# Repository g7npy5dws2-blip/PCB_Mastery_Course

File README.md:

# PCB_Mastery_Course
Here will be all the documents assosiated with the PCB_Mastery_Course

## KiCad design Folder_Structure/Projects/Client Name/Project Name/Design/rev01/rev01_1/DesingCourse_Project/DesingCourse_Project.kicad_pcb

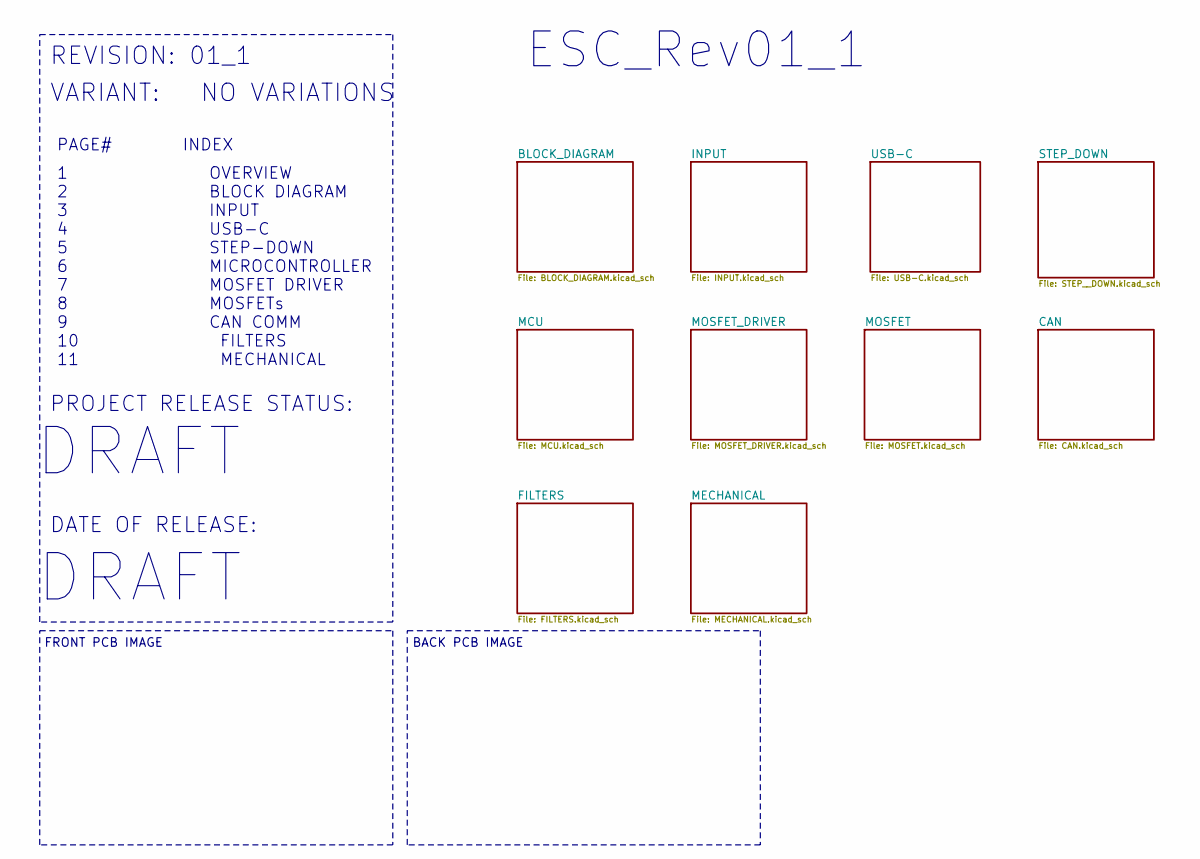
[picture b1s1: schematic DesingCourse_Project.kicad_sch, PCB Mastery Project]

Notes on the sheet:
VARIANT:
NO VARIATIONS
1 OVERVIEW 2 BLOCK DIAGRAM 3 INPUT 4 USB-C 5 STEP-DOWN 6 MICROCONTROLLER 7 MOSFET DRIVER 8 MOSFETs 9 CAN COMM 10 FILTERS 11 MECHANICAL
PAGE# INDEX
DRAFT
PROJECT RELEASE STATUS: DATE OF RELEASE:
ESC_Rev01_1
FRONT PCB IMAGE
REVISION: ${REVISION}
BACK PCB IMAGE

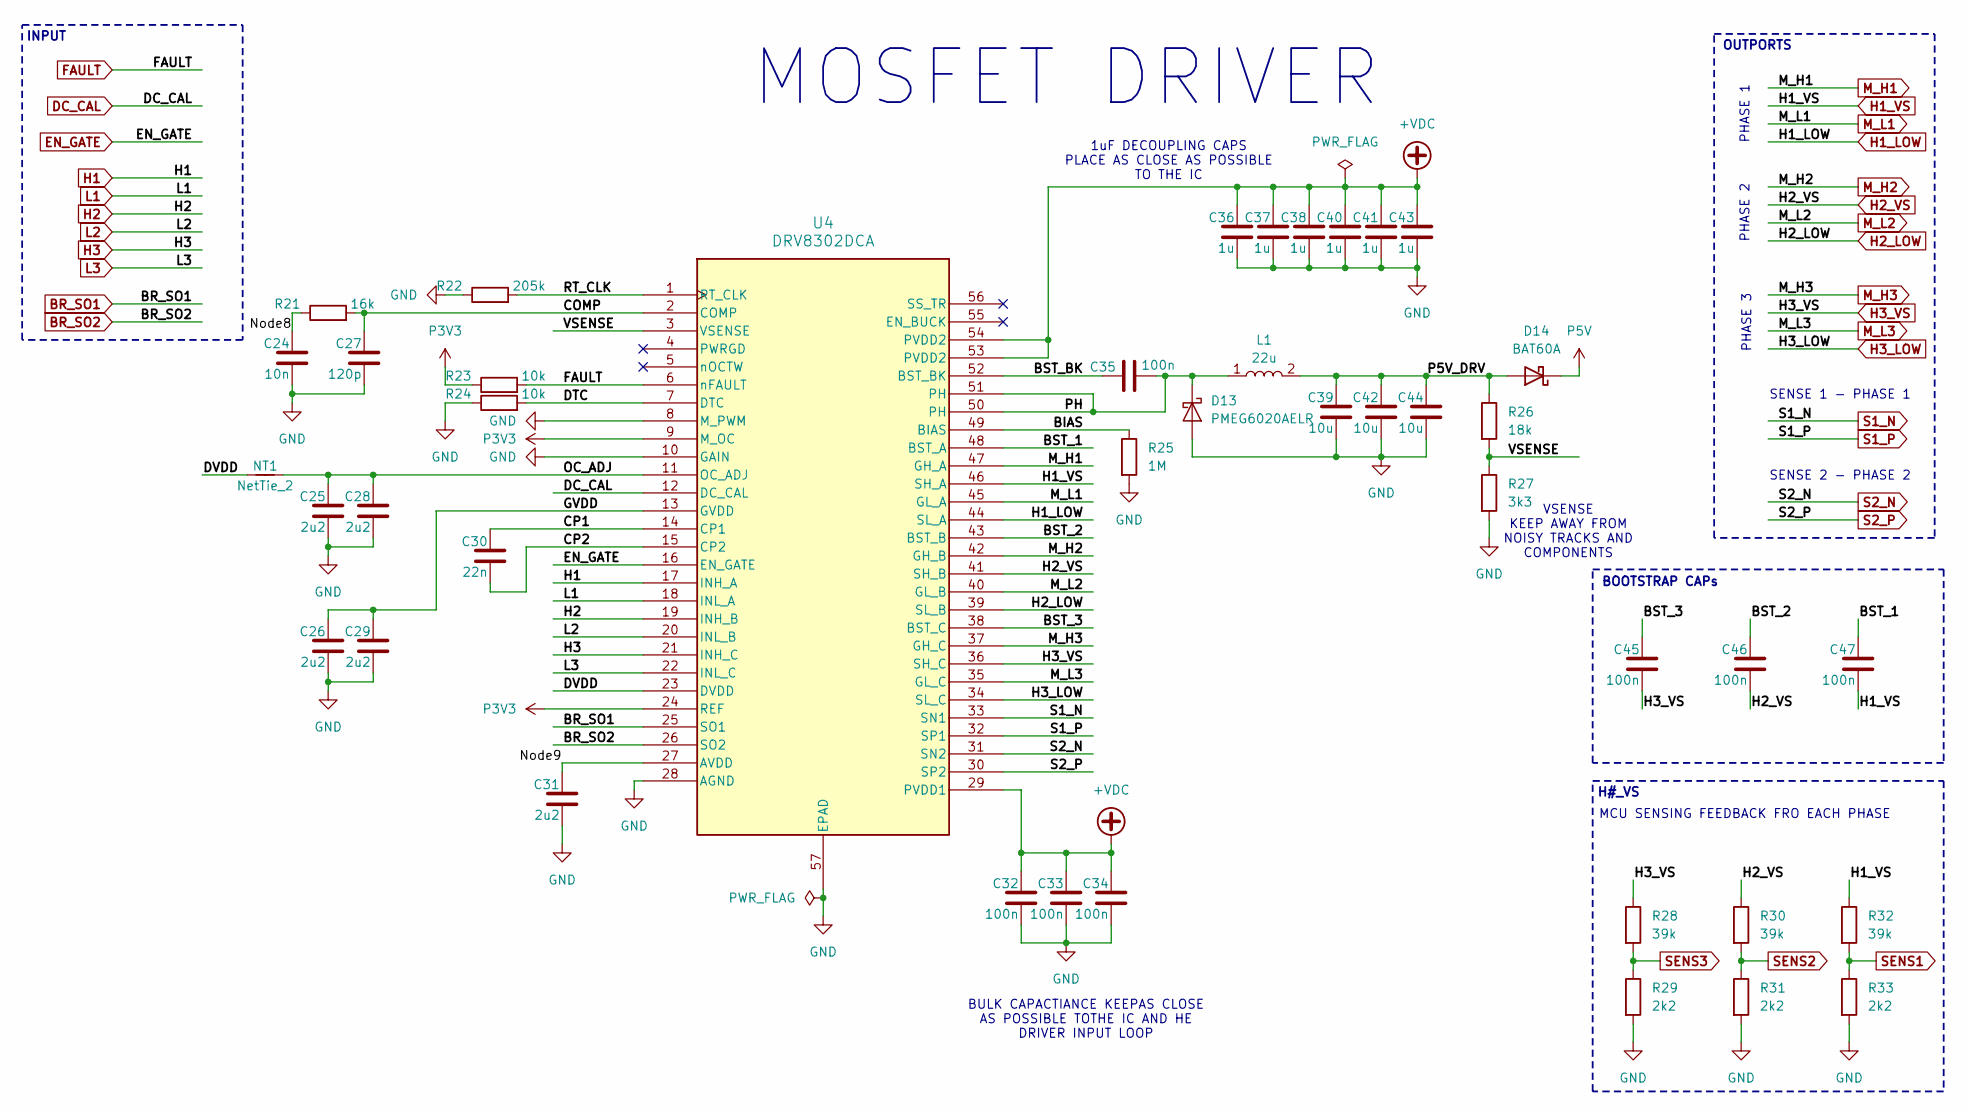
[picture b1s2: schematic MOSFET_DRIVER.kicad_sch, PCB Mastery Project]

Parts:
C24: 10n; C_0603_1608Metric; Voltage Rating 50V; Tolerance 10%
C25, C26, C28, C29, C31: 2u2; C_0603_1608Metric; Voltage Rating 6.3V; Tolerance 10%
C27: 120p; C_0603_1608Metric; Voltage Rating 50V; Tolerance 10%
C30: 22n; C_0603_1608Metric; Voltage Rating 100V; Tolerance 10%
C32, C33, C34, C35, C45, C46, C47: 100n; C_0603_1608Metric; Voltage Rating 10V; Tolerance 10%
C36, C37, C38, C40, C41, C43: 1u; C_0603_1608Metric; Voltage Rating 100V; Tolerance 10%
C39, C42, C44: 10u; C_1210_3225Metric; Voltage Rating 16V; Tolerance 10%
D13: PMEG6020AELR; Nexperia_CFP3_SOD-123W; MPN PMEG6020AELR
D14: BAT60A; D_SOD-323; MPN BAT60A
L1: 22u; IND_BOURNS_SDR0805; MPN SDR0805-220ML
NT1: NetTie_2; NetTie-2_SMD_Pad0.5mm
R21: 16k; R_0603_1608Metric; Tolerance 1%; Power Rating 1/10W
R22: 205k; R_0603_1608Metric; Tolerance 1%; Power Rating 1/10W
R23, R24: 10k; R_0603_1608Metric; Tolerance 1%; Power Rating 1/10W
R25: 1M; R_0603_1608Metric; Tolerance 1%; Power Rating 1/10W
R26: 18k; R_0603_1608Metric; Tolerance 1%; Power Rating 1/10W
R27: 3k3; R_0603_1608Metric; Tolerance 1%; Power Rating 1/10W
R28, R30, R32: 39k; R_0603_1608Metric; Tolerance 1%; Power Rating 1/10W
R29, R31, R33: 2k2; R_0603_1608Metric; Tolerance 1%; Power Rating 1/10W
U4: DRV8302DCA; SOP50P810X120-57N; MPN DRV8302DCA

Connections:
+VDC: C32.1, C33.1, C34.1, C36.1, C37.1, C38.1, C40.1, C41.1, C43.1, U4.29 (PVDD1), U4.53 (PVDD2), U4.54 (PVDD2); also elsewhere on the board
/MOSFET_DRIVER/BIAS: R25.1, U4.49 (BIAS)
/MOSFET_DRIVER/BST_1: C47.1, U4.48 (BST_A)
/MOSFET_DRIVER/BST_2: C46.1, U4.43 (BST_B)
/MOSFET_DRIVER/BST_3: C45.1, U4.38 (BST_C)
/MOSFET_DRIVER/BST_BK: C35.1, U4.52 (BST_BK)
/MOSFET_DRIVER/COMP: C27.1, R21.2, U4.2 (COMP)
/MOSFET_DRIVER/CP1: C30.1, U4.14 (CP1)
/MOSFET_DRIVER/CP2: C30.2, U4.15 (CP2)
/MOSFET_DRIVER/DTC: R24.2, U4.7 (DTC)
/MOSFET_DRIVER/DVDD: NT1.1, U4.23 (DVDD)
/MOSFET_DRIVER/GVDD: C26.1, C29.1, U4.13 (GVDD)
/MOSFET_DRIVER/Node8: C24.1, R21.1
/MOSFET_DRIVER/Node9: C31.1, U4.27 (AVDD)
/MOSFET_DRIVER/OC_ADJ: C25.1, C28.1, NT1.2, U4.11 (OC_ADJ)
/MOSFET_DRIVER/P5V_DRV: C39.1, C42.1, C44.1, D14.2 (A), L1.2, R26.1
/MOSFET_DRIVER/PH: C35.2, D13.1 (K), L1.1, U4.50 (PH), U4.51 (PH)
/MOSFET_DRIVER/RT_CLK: R22.2, U4.1 (RT_CLK)
/MOSFET_DRIVER/VSENSE: R26.2, R27.1, U4.3 (VSENSE)
BR_SO1: U4.25 (SO1); also elsewhere on the board
BR_SO2: U4.26 (SO2); also elsewhere on the board
DC_CAL: U4.12 (DC_CAL); also elsewhere on the board
EN_GATE: U4.16 (EN_GATE); also elsewhere on the board
FAULT: R23.2, U4.6 (nFAULT); also elsewhere on the board
GND: C24.2, C25.2, C26.2, C27.2, C28.2, C29.2, C31.2, C32.2, C33.2, C34.2, C36.2, C37.2, C38.2, C39.2, C40.2, C41.2, C42.2, C43.2, C44.2, D13.2 (A), R22.1, R24.1, R25.2, R27.2, R29.2, R31.2, R33.2, U4.8 (M_PWM), U4.10 (GAIN), U4.28 (AGND), U4.57 (EPAD); also elsewhere on the board
H1: U4.17 (INH_A); also elsewhere on the board
H1_LOW: U4.44 (SL_A); also elsewhere on the board
H1_VS: C47.2, R32.1, U4.46 (SH_A); also elsewhere on the board
H2: U4.19 (INH_B); also elsewhere on the board
H2_LOW: U4.39 (SL_B); also elsewhere on the board
H2_VS: C46.2, R30.1, U4.41 (SH_B); also elsewhere on the board
H3: U4.21 (INH_C); also elsewhere on the board
H3_LOW: U4.34 (SL_C); also elsewhere on the board
H3_VS: C45.2, R28.1, U4.36 (SH_C); also elsewhere on the board
L1: U4.18 (INL_A); also elsewhere on the board
L2: U4.20 (INL_B); also elsewhere on the board
L3: U4.22 (INL_C); also elsewhere on the board
M_H1: U4.47 (GH_A); also elsewhere on the board
M_H2: U4.42 (GH_B); also elsewhere on the board
M_H3: U4.37 (GH_C); also elsewhere on the board
M_L1: U4.45 (GL_A); also elsewhere on the board
M_L2: U4.40 (GL_B); also elsewhere on the board
M_L3: U4.35 (GL_C); also elsewhere on the board
P3V3: R23.1, U4.9 (M_OC), U4.24 (REF); also elsewhere on the board
P5V: D14.1 (K); also elsewhere on the board
S1_N: U4.33 (SN1); also elsewhere on the board
S1_P: U4.32 (SP1); also elsewhere on the board
S2_N: U4.31 (SN2); also elsewhere on the board
S2_P: U4.30 (SP2); also elsewhere on the board
SENS1: R32.2, R33.1; also elsewhere on the board
SENS2: R30.2, R31.1; also elsewhere on the board
SENS3: R28.2, R29.1; also elsewhere on the board

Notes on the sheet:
SENSE 2 - PHASE 2
PHASE 2
OUTPORTS
BOOTSTRAP CAPs
1uF DECOUPLING CAPS PLACE AS CLOSE AS POSSIBLE TO THE IC
PHASE 3
PHASE 1
MOSFET DRIVER
SENSE 1 - PHASE 1
BULK CAPACTIANCE KEEPAS CLOSE AS POSSIBLE TOTHE IC AND HE DRIVER INPUT LOOP
H#_VS
INPUT
VSENSE KEEP AWAY FROM NOISY TRACKS AND COMPONENTS
MCU SENSING FEEDBACK FRO EACH PHASE

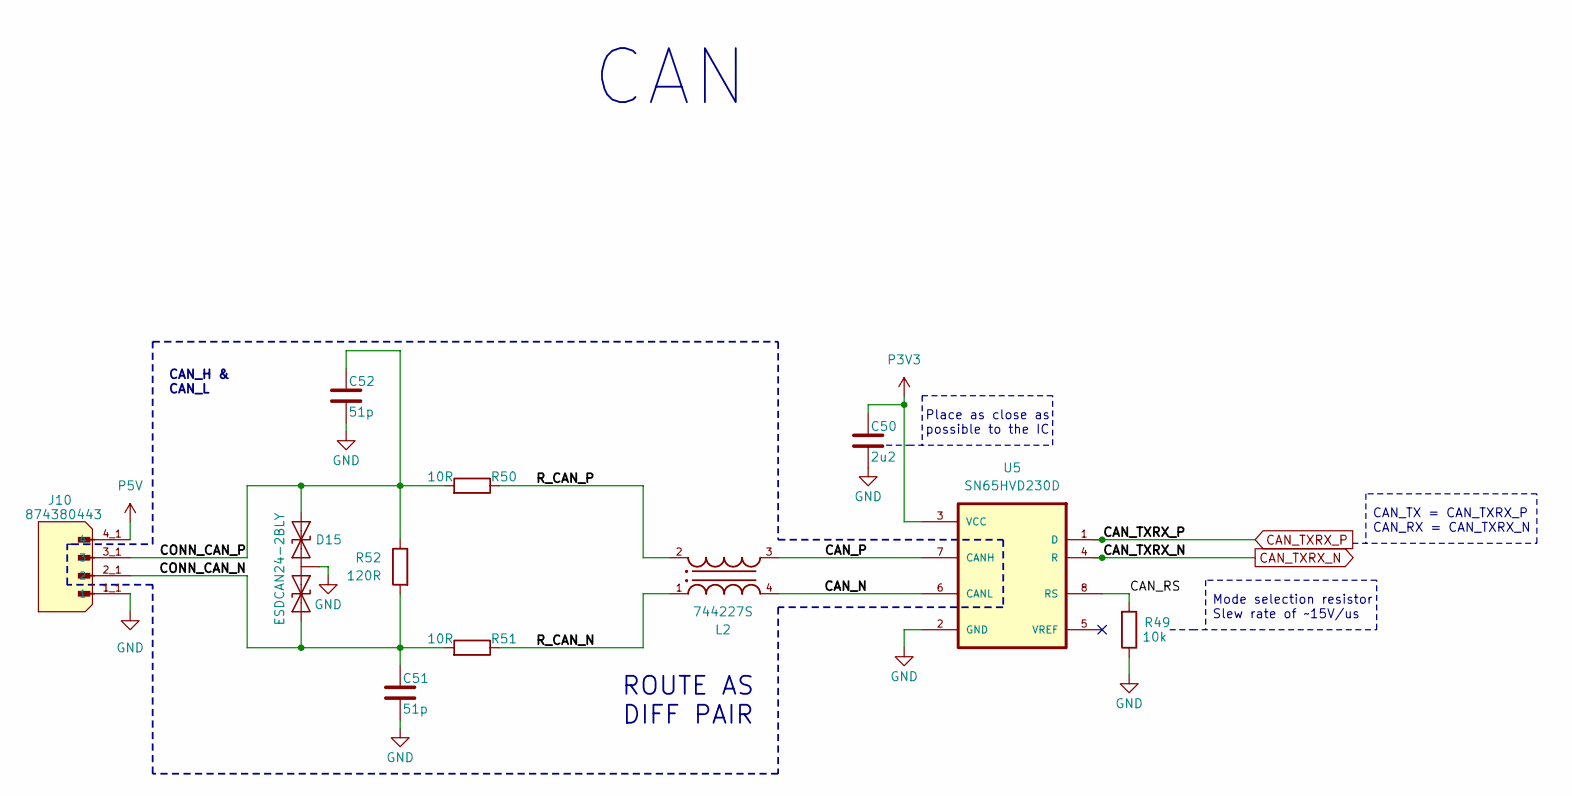
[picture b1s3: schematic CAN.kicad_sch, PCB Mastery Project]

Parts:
C50: 2u2; C_0603_1608Metric; Voltage Rating 6.3V; Tolerance 10%
C51, C52: 51p; C_0603_1608Metric; Voltage Rating 50V; Tolerance 10%
D15: ESDCAN24-2BLY; SOT95P237X112-3N; MPN ESDCAN24-2BLY
J10: 874380443; MOLEX_874380443; MPN 874380843
L2: 744227S; WE-SL2; MPN 744227S
R49: 10k; R_0603_1608Metric; Tolerance 1%; Power Rating 1/10W
R50, R51: 10R; R_0603_1608Metric; Tolerance 1%; Power Rating 1/10W
R52: 120R; R_0603_1608Metric; Tolerance 1%; Power Rating 1/10W
U5: SN65HVD230D; SOIC127P599X175-8N; MPN SN65HVD230D

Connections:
/CAN/CAN_N: L2.4, U5.6 (CANL)
/CAN/CAN_P: L2.3, U5.7 (CANH)
/CAN/CAN_RS: R49.2, U5.8 (RS)
/CAN/CONN_CAN_N: C51.1, D15.1 (A1), J10.2_1 (2), J10.2_2 (2), R51.2, R52.2
/CAN/CONN_CAN_P: C52.1, D15.2 (A2), J10.3_1 (3), J10.3_2 (3), R50.2, R52.1
/CAN/R_CAN_N: L2.1, R51.1
/CAN/R_CAN_P: L2.2, R50.1
CAN_TXRX_N: U5.4 (R); also elsewhere on the board
CAN_TXRX_P: U5.1 (D); also elsewhere on the board
GND: C50.2, C51.2, C52.2, D15.3 (C), J10.1_1 (1), J10.1_2 (1), R49.1, U5.2 (GND); also elsewhere on the board
P3V3: C50.1, U5.3 (VCC); also elsewhere on the board
P5V: J10.4_1 (4), J10.4_2 (4); also elsewhere on the board

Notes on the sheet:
CAN
Mode selection resistor Slew rate of ~15V/us
CAN_H & CAN_L
CAN_TX = CAN_TXRX_P CAN_RX = CAN_TXRX_N
ROUTE AS DIFF PAIR
Place as close as possible to the IC

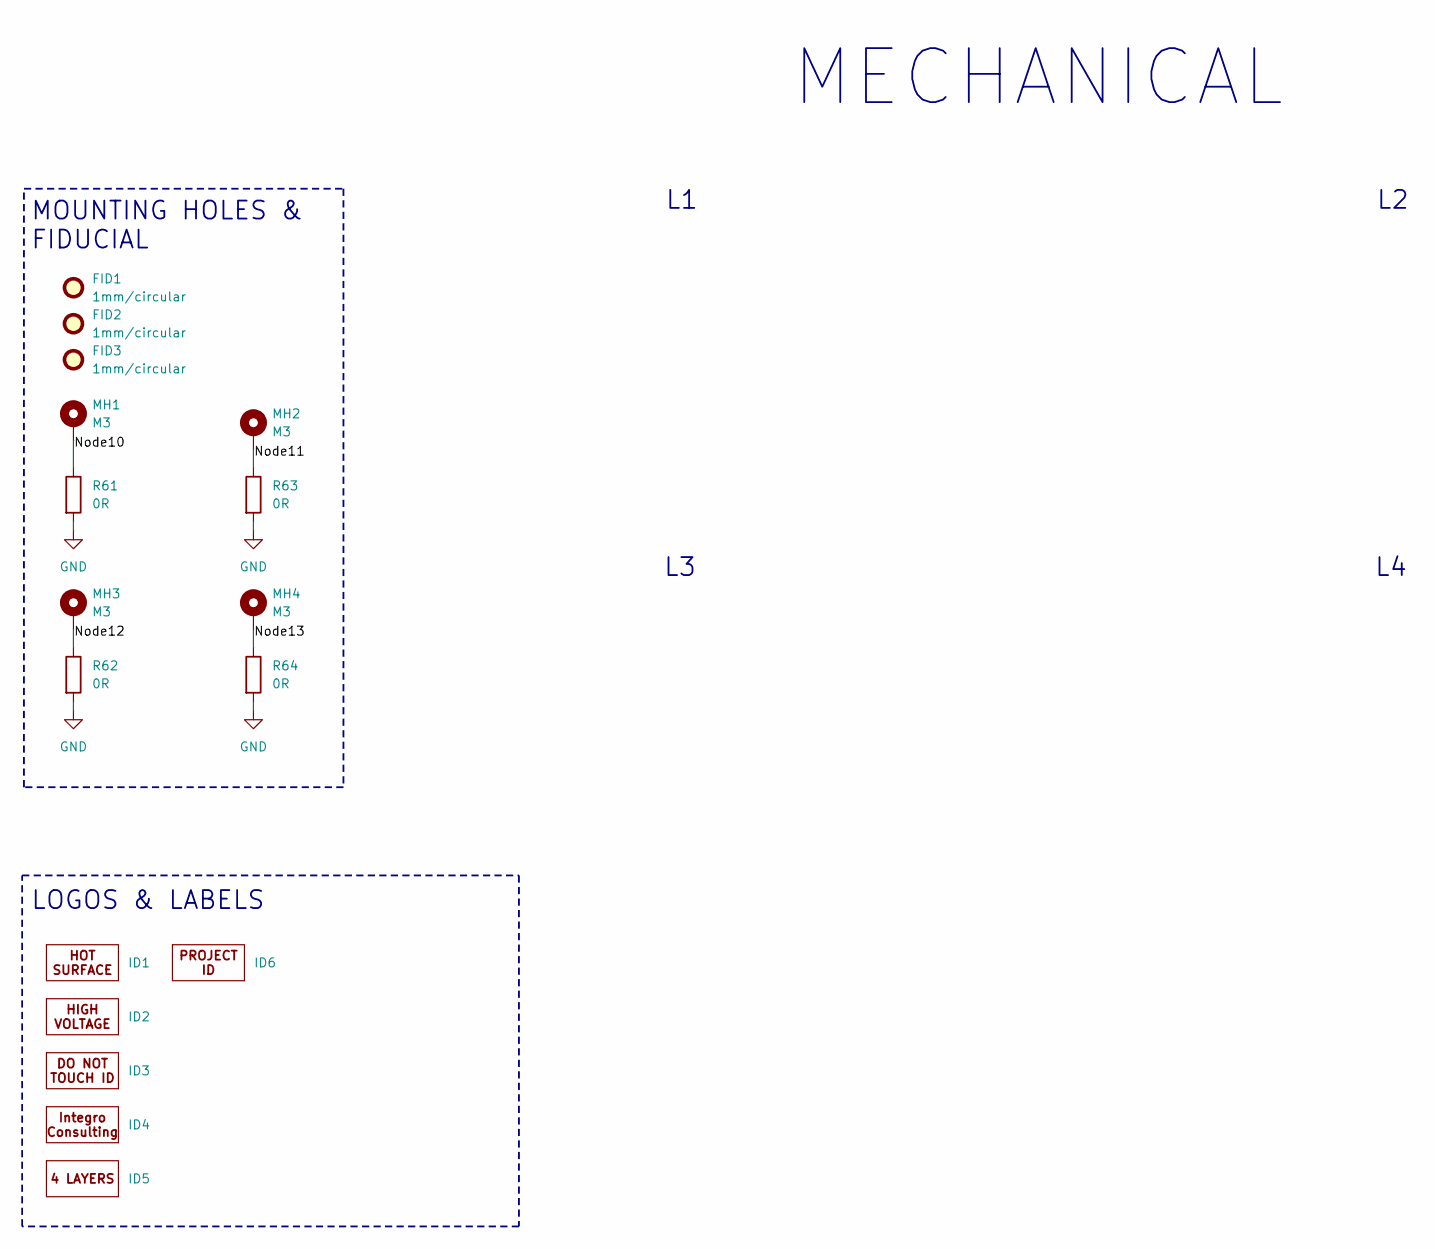
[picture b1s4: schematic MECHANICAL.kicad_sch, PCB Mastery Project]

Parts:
FID1, FID2, FID3: 1mm/circular; Fiducial_1mm_Mask2mm
ID1: hot-surface
ID2: high-voltage
ID3: ESD-suceptible
ID4: IC-logo
ID5: 4_Layer_ID
ID6: Project_ID
MH1, MH2, MH3, MH4: M3; MountingHole_3mm_Pad_Via
R61, R62, R63, R64: 0R; R_0603_1608Metric; Tolerance 1%; Power Rating 1/10W

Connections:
/MECHANICAL/Node10: MH1.1, R61.1
/MECHANICAL/Node11: MH2.1, R63.1
/MECHANICAL/Node12: MH3.1, R62.1
/MECHANICAL/Node13: MH4.1, R64.1
GND: R61.2, R62.2, R63.2, R64.2; also elsewhere on the board

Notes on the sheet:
MOUNTING HOLES & FIDUCIAL
MECHANICAL
LOGOS & LABELS

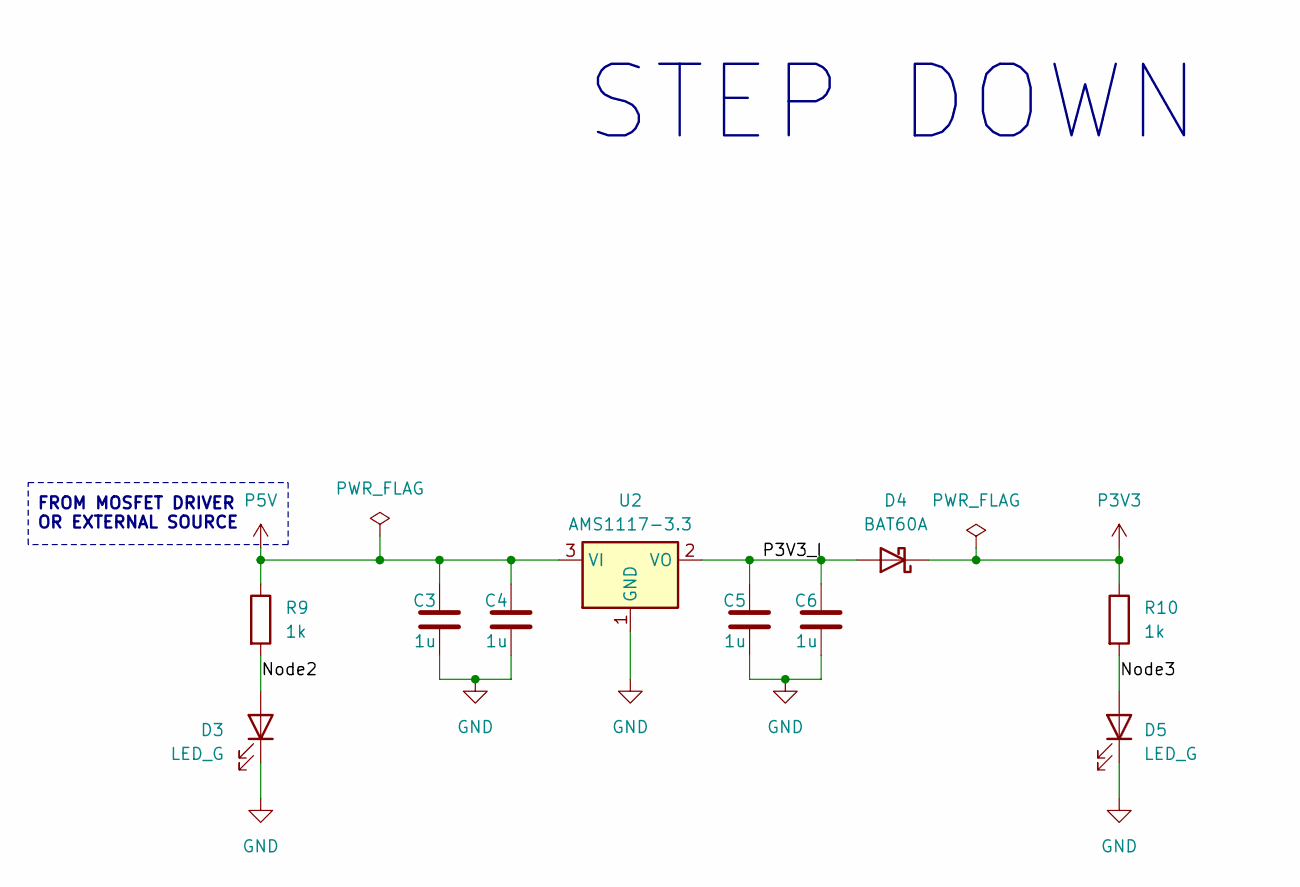
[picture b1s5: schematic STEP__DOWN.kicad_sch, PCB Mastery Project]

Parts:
C3, C4, C5, C6: 1u; C_0603_1608Metric; Voltage Rating 10V; Tolerance 10%
D3, D5: LED_G; D_1206_3216Metric; MPN 15-21/GHC-XS1T1/2T
D4: BAT60A; D_SOD-323; MPN BAT60A
R9, R10: 1k; R_0603_1608Metric; Tolerance 1%; Power Rating 1/10W
U2: AMS1117-3.3; SOT-223-3_TabPin2; MPN AMS1117-3.3

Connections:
/STEP_DOWN/Node2: D3.2 (A), R9.2
/STEP_DOWN/Node3: D5.2 (A), R10.2
/STEP_DOWN/P3V3_I: C5.1, C6.1, D4.2 (A), U2.2 (VO)
GND: C3.2, C4.2, C5.2, C6.2, D3.1 (K), D5.1 (K), U2.1 (GND); also elsewhere on the board
P3V3: D4.1 (K), R10.1; also elsewhere on the board
P5V: C3.1, C4.1, R9.1, U2.3 (VI); also elsewhere on the board

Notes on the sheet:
FROM MOSFET DRIVER OR EXTERNAL SOURCE
STEP DOWN

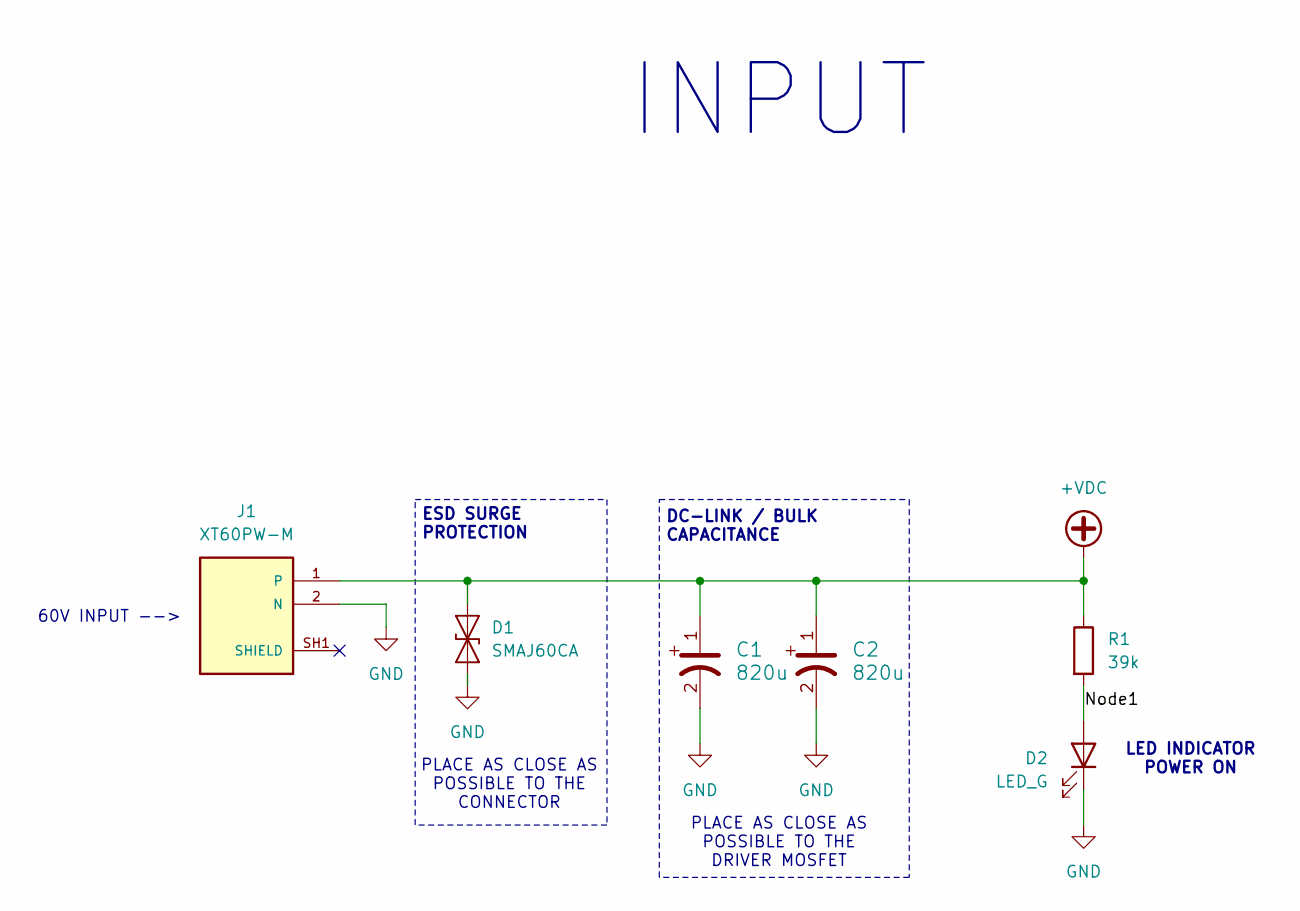
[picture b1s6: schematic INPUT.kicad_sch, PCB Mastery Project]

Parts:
C1, C2: 820u; RA_LKMI2501K821MF_YMIN; Tolerance 20%; Voltage Rating 80V; MPN LKMI2501K821MF
D1: SMAJ60CA; D_SMA; MPN SMAJ60CA
D2: LED_G; D_1206_3216Metric; MPN 15-21/GHC-XS1T1/2T
J1: XT60PW-M; AMASS_XT60PW-M; MPN XT60PW-M
R1: 39k; R_0603_1608Metric; Tolerance 1%; Power Rating 1/10W

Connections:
+VDC: C1.1, C2.1, D1.2 (A2), J1.1, R1.1; also elsewhere on the board
/INPUT/Node1: D2.2 (A), R1.2
GND: C1.2, C2.2, D1.1 (A1), D2.1 (K), J1.2 (N); also elsewhere on the board

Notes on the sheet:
PLACE AS CLOSE AS POSSIBLE TO THE CONNECTOR
ESD SURGE PROTECTION
LED INDICATOR POWER ON
DC-LINK / BULK CAPACITANCE
60V INPUT -->
INPUT
PLACE AS CLOSE AS POSSIBLE TO THE DRIVER MOSFET

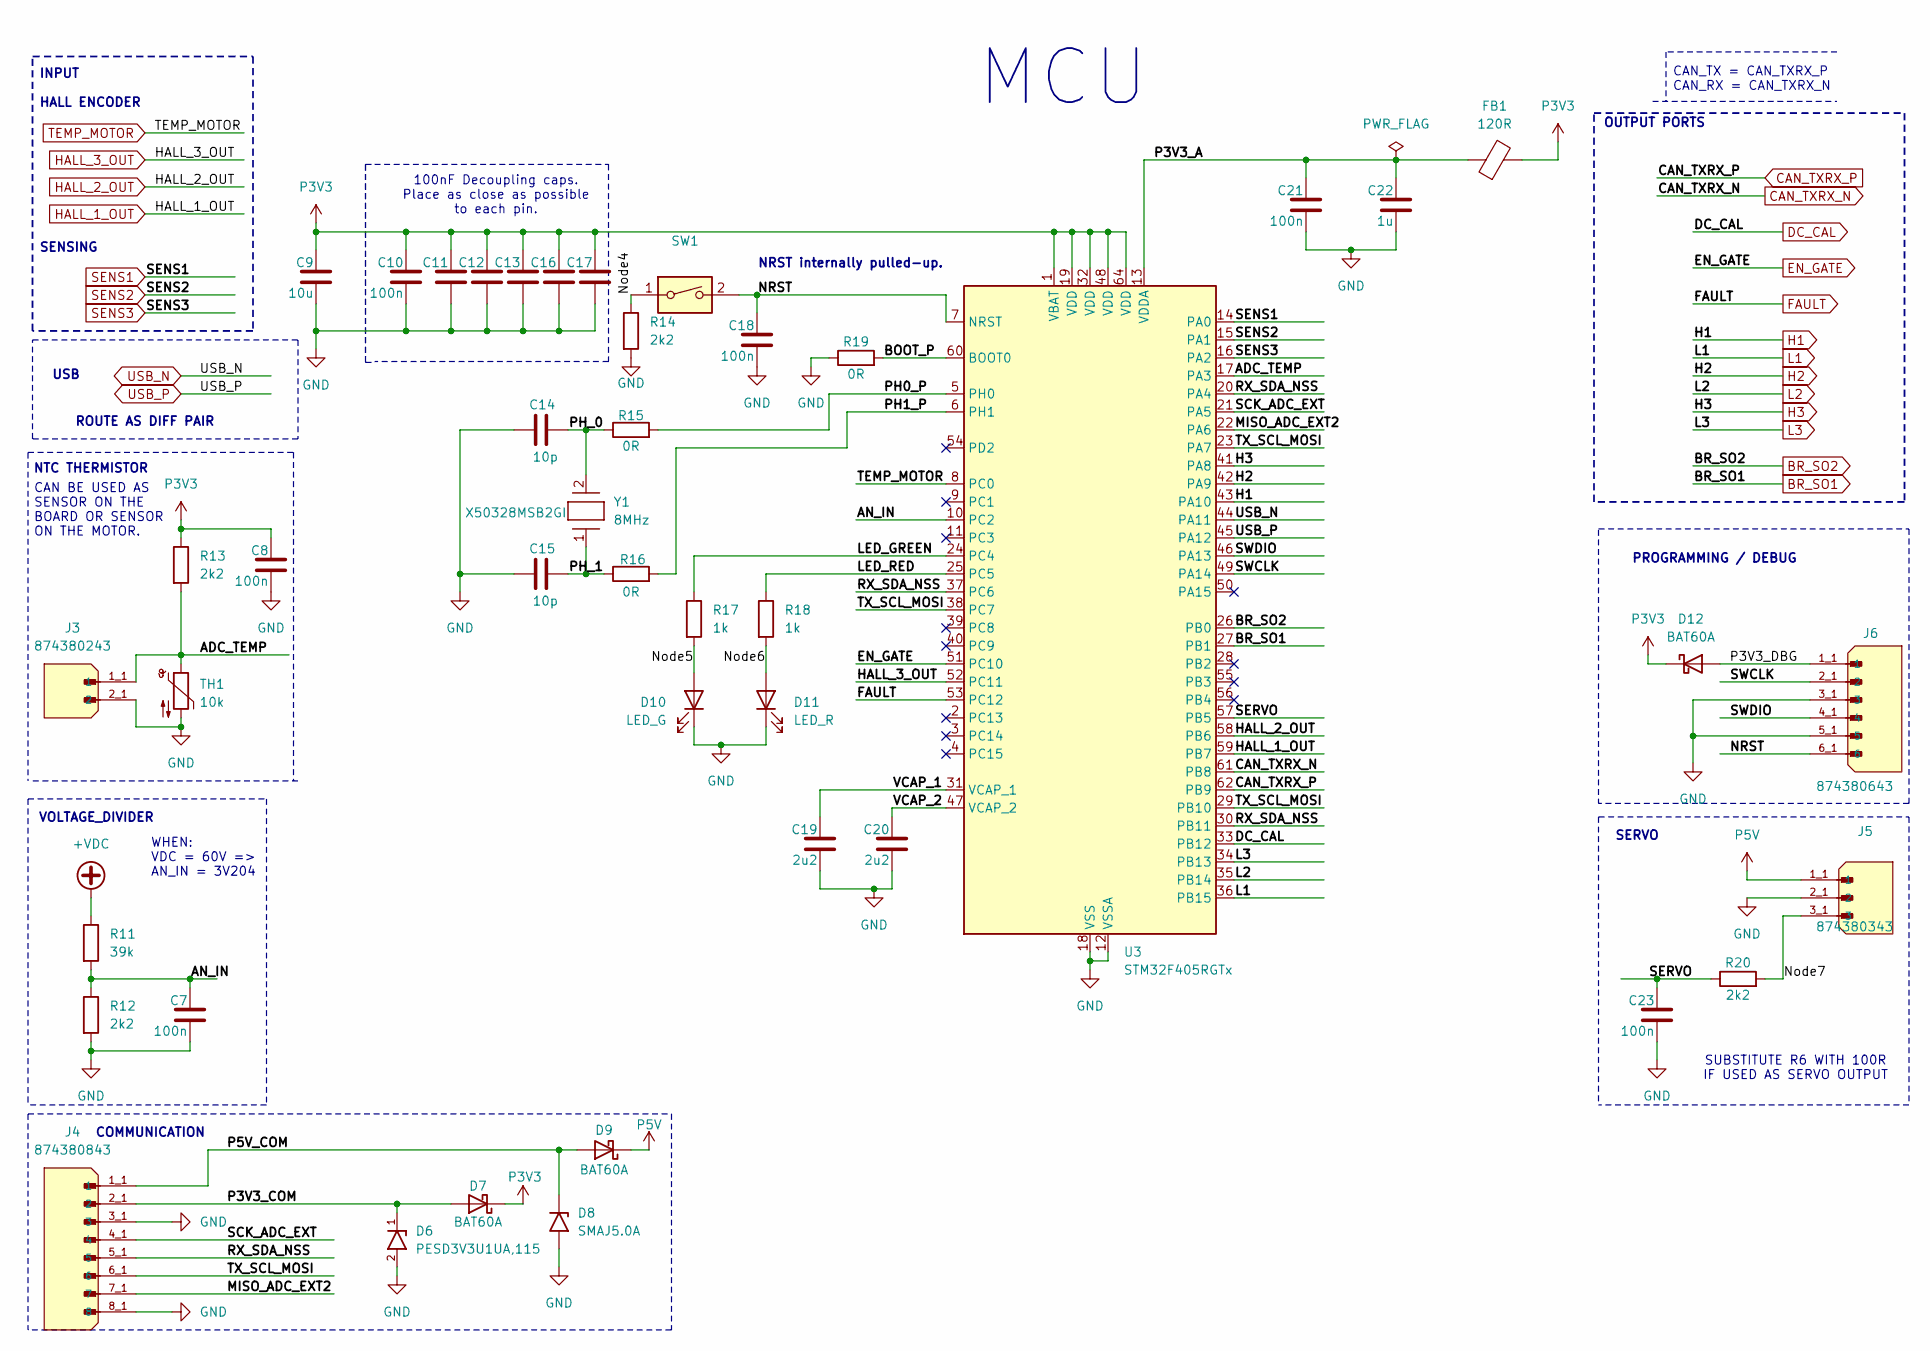
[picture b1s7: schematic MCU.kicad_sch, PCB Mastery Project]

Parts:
C7, C8, C10, C11, C12, C13, C16, C17, C18, C21, C23: 100n; C_0603_1608Metric; Voltage Rating 10V; Tolerance 10%
C9: 10u; C_0603_1608Metric; Voltage Rating 10V; Tolerance 10%
C14, C15: 10p; C_0603_1608Metric; Voltage Rating 50V; Tolerance 10%
C19, C20: 2u2; C_0603_1608Metric; Voltage Rating 6.3V; Tolerance 10%
C22: 1u; C_0603_1608Metric; Voltage Rating 10V; Tolerance 10%
D6: PESD3V3U1UA,115; DIO_PESD3V3U1UA_115; MPN PESD3V3U1UA,115
D7, D9, D12: BAT60A; D_SOD-323; MPN BAT60A
D8: SMAJ5.0A; D_SMA; MPN SMAJ5.0A
D10: LED_G; D_1206_3216Metric; MPN 15-21/GHC-XS1T1/2T
D11: LED_R; D_1206_3216Metric; MPN 15-21/R6C-FQ1R1B/2T
FB1: 120R; BEADC1608X95N; MPN BLM18PG121SN1D
J3: 874380243; MOLEX_874380243; MPN 874380243
J4: 874380843; MOLEX_874380843; MPN 874380843
J5: 874380343; MOLEX_874380343; MPN 874380343
J6: 874380643; MOLEX_874380643; MPN 874380843
R11: 39k; R_0603_1608Metric; Tolerance 1%; Power Rating 1/10W
R12, R13, R14, R20: 2k2; R_0603_1608Metric; Tolerance 1%; Power Rating 1/10W
R15, R16, R19: 0R; R_0603_1608Metric; Tolerance 1%; Power Rating 1/10W
R17, R18: 1k; R_0603_1608Metric; Tolerance 1%; Power Rating 1/10W
SW1: SMT_FS; MPN PTS526SK15SMTR2 LFS
TH1: 10k; R_0603_1608Metric; Tolerance 1%; MPN NCP18XH103F03RB
U3: STM32F405RGTx; LQFP-64_10x10mm_P0.5mm; MPN STM32F405RGTx
Y1: 8MHz; XTAL_MSB2GI_YXC; MPN X50328MSB2GI

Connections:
+VDC: R11.1; also elsewhere on the board
/MCU/ADC_TEMP: J3.1_1 (1), J3.1_2 (1), R13.2, TH1.1, U3.17 (PA3)
/MCU/AN_IN: C7.1, R11.2, R12.1, U3.10 (PC2)
/MCU/BOOT_P: R19.2, U3.60 (BOOT0)
/MCU/LED_GREEN: R17.1, U3.24 (PC4)
/MCU/LED_RED: R18.1, U3.25 (PC5)
/MCU/MISO_ADC_EXT2: J4.7_1 (7), J4.7_2 (7), U3.22 (PA6)
/MCU/NRST: C18.1, J6.6_1 (6), J6.6_2 (6), SW1.2, U3.7 (NRST)
/MCU/Node4: R14.1, SW1.1
/MCU/Node5: D10.2 (A), R17.2
/MCU/Node6: D11.2 (A), R18.2
/MCU/Node7: J5.3_1 (3), J5.3_2 (3), R20.2
/MCU/P3V3_A: C21.1, C22.1, FB1.1, U3.13 (VDDA)
/MCU/P3V3_COM: D6.1, D7.2 (A), J4.2_1 (2), J4.2_2 (2)
/MCU/P3V3_DBG: D12.2 (A), J6.1_1 (1), J6.1_2 (1)
/MCU/P5V_COM: D8.1 (A1), D9.2 (A), J4.1_1 (1), J4.1_2 (1)
/MCU/PH0_P: R15.2, U3.5 (PH0)
/MCU/PH1_P: R16.2, U3.6 (PH1)
/MCU/PH_0: C14.1, R15.1, Y1.2
/MCU/PH_1: C15.1, R16.1, Y1.1
/MCU/RX_SDA_NSS: J4.5_1 (5), J4.5_2 (5), U3.20 (PA4), U3.30 (PB11), U3.37 (PC6)
/MCU/SCK_ADC_EXT: J4.4_1 (4), J4.4_2 (4), U3.21 (PA5)
/MCU/SERVO: C23.1, R20.1, U3.57 (PB5)
/MCU/SWCLK: J6.2_1 (2), J6.2_2 (2), U3.49 (PA14)
/MCU/SWDIO: J6.4_1 (4), J6.4_2 (4), U3.46 (PA13)
/MCU/TX_SCL_MOSI: J4.6_1 (6), J4.6_2 (6), U3.23 (PA7), U3.29 (PB10), U3.38 (PC7)
/MCU/VCAP_1: C19.1, U3.31 (VCAP_1)
/MCU/VCAP_2: C20.1, U3.47 (VCAP_2)
BR_SO1: U3.27 (PB1); also elsewhere on the board
BR_SO2: U3.26 (PB0); also elsewhere on the board
CAN_TXRX_N: U3.61 (PB8); also elsewhere on the board
CAN_TXRX_P: U3.62 (PB9); also elsewhere on the board
DC_CAL: U3.33 (PB12); also elsewhere on the board
EN_GATE: U3.51 (PC10); also elsewhere on the board
FAULT: U3.53 (PC12); also elsewhere on the board
GND: C7.2, C8.2, C9.2, C10.2, C11.2, C12.2, C13.2, C14.2, C15.2, C16.2, C17.2, C18.2, C19.2, C20.2, C21.2, C22.2, C23.2, D6.2, D8.2 (A2), D10.1 (K), D11.1 (K), J3.2_1 (2), J3.2_2 (2), J4.3_1 (3), J4.3_2 (3), J4.8_1 (8), J4.8_2 (8), J5.2_1 (2), J5.2_2 (2), J6.3_1 (3), J6.3_2 (3), J6.5_1 (5), J6.5_2 (5), R12.2, R14.2, R19.1, TH1.2, U3.12 (VSSA), U3.18 (VSS), U3.63 (VSS); also elsewhere on the board
H1: U3.43 (PA10); also elsewhere on the board
H2: U3.42 (PA9); also elsewhere on the board
H3: U3.41 (PA8); also elsewhere on the board
HALL_1_OUT: U3.59 (PB7); also elsewhere on the board
HALL_2_OUT: U3.58 (PB6); also elsewhere on the board
HALL_3_OUT: U3.52 (PC11); also elsewhere on the board
L1: U3.36 (PB15); also elsewhere on the board
L2: U3.35 (PB14); also elsewhere on the board
L3: U3.34 (PB13); also elsewhere on the board
P3V3: C8.1, C9.1, C10.1, C11.1, C12.1, C13.1, C16.1, C17.1, D7.1 (K), D12.1 (K), FB1.2, R13.1, U3.1 (VBAT), U3.19 (VDD), U3.32 (VDD), U3.48 (VDD), U3.64 (VDD); also elsewhere on the board
P5V: D9.1 (K), J5.1_1 (1), J5.1_2 (1); also elsewhere on the board
SENS1: U3.14 (PA0); also elsewhere on the board
SENS2: U3.15 (PA1); also elsewhere on the board
SENS3: U3.16 (PA2); also elsewhere on the board
TEMP_MOTOR: U3.8 (PC0); also elsewhere on the board
USB_N: U3.44 (PA11); also elsewhere on the board
USB_P: U3.45 (PA12); also elsewhere on the board

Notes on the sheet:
CAN BE USED AS SENSOR ON THE BOARD OR SENSOR ON THE MOTOR.
PROGRAMMING / DEBUG
NRST internally pulled-up.
USB
MCU
CAN_TX = CAN_TXRX_P CAN_RX = CAN_TXRX_N
WHEN: VDC = 60V => AN_IN = 3V204
NTC THERMISTOR
INPUT HALL ENCODER SENSING
OUTPUT PORTS
ROUTE AS DIFF PAIR
SERVO
SUBSTITUTE R6 WITH 100R IF USED AS SERVO OUTPUT
VOLTAGE_DIVIDER
100nF Decoupling caps. Place as close as possible to each pin.
COMMUNICATION

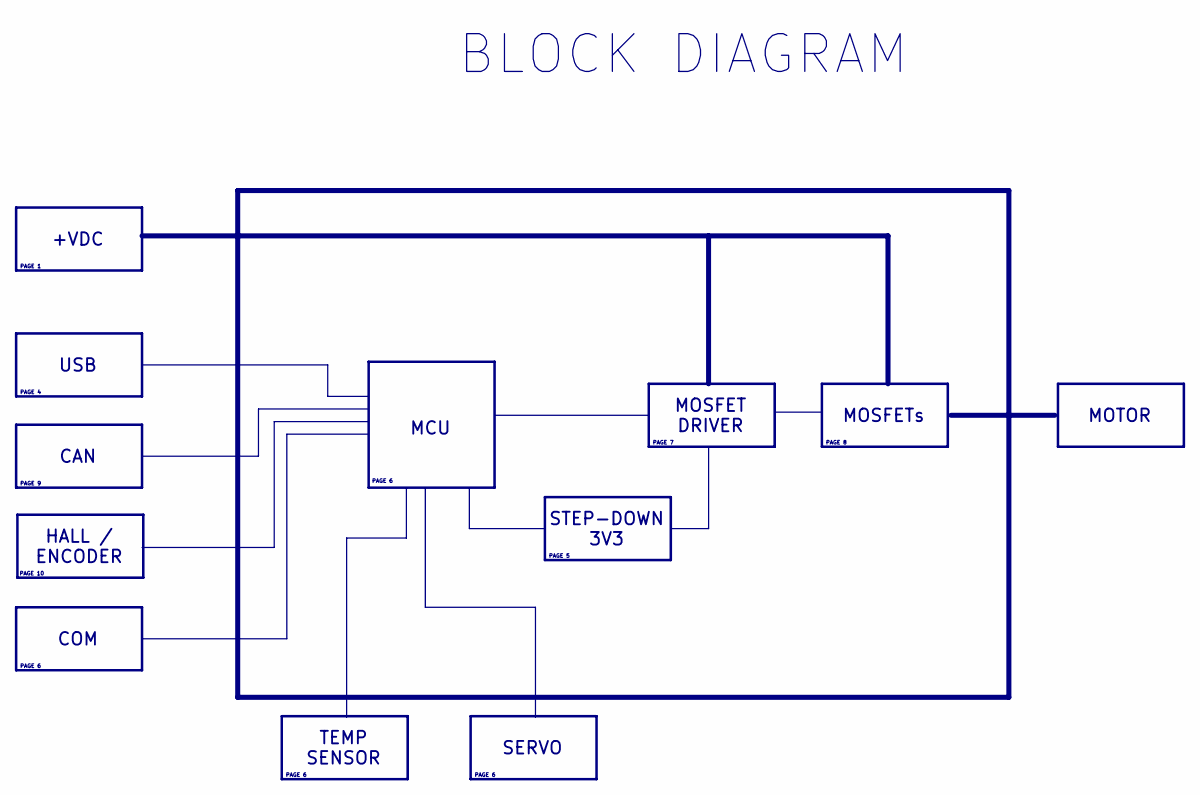
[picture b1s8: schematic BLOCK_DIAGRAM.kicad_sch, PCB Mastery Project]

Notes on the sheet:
STEP-DOWN 3V3
PAGE 6
TEMP SENSOR
PAGE 10
COM
PAGE 4
PAGE 9
PAGE 5
MOSFET DRIVER
PAGE 8
MOSFETs
+VDC
BLOCK DIAGRAM
USB
MCU
MOTOR
SERVO
CAN
PAGE 1
PAGE 7
HALL / ENCODER

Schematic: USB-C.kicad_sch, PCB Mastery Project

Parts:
J2: TYPE-C-31-M-12; HRO_TYPE-C-31-M-12; MPN TYPE-C-31-M-12
R2, R3, R4: 0R; R_0603_1608Metric; Tolerance 1%; Power Rating 1/10W
R5, R6: 5k1; R_0603_1608Metric; Tolerance 1%; Power Rating 1/10W
R7, R8: 22R; R_0603_1608Metric; Tolerance 1%; Power Rating 1/10W
U1: PUSB3AB6Z; IC_PUSB3AB6Z; MPN PUSB3AB6Z

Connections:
/USB-C/CC1: J2.A5 (CC1), R5.1, U1.4 (CH3)
/USB-C/CC2: J2.B5 (CC2), R6.1, U1.1 (CH1)
/USB-C/Shield_USB: J2.S1 (SHIELD), J2.S2 (SHIELD), J2.S3 (SHIELD), J2.S4 (SHIELD), R2.1, R3.1
/USB-C/USB-C_N: J2.A7 (DN1), J2.B7 (DN2), R7.1, U1.6 (CH5)
/USB-C/USB-C_P: J2.A6 (DP1), J2.B6 (DP2), R8.1, U1.7 (CH6)
GND: J2.A1_B12 (GND), J2.B1_A12 (GND), R2.2, R3.2, R5.2, R6.2, U1.2 (GND); also elsewhere on the board
P5V: R4.1; also elsewhere on the board
USB_N: R7.2; also elsewhere on the board
USB_P: R8.2; also elsewhere on the board
VBUS: J2.A4_B9 (VBUS), J2.B4_A9 (VBUS), R4.2, U1.3 (CH2), U1.5 (CH4)

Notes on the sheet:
USB TYPE - C ONLY 2.0
USB TO MCU
USB-C
PULL-DOWN, TELL THE HOST WE ARE UFP. ONLY ONE USED AT GIVEN TIME. BOTH NECESSARY FOR REVERSIBILTY.
FIT A ZERO OHM LINK, CAP, OR RESISTOR
TERMINATION RESISTORS. PLACE AS CLOSE AS POSSIBLE TO THE MCU.
ROUTE AS DIFF PAIR
MOUNT A 0R JUMPER IF USD AS USB HOST

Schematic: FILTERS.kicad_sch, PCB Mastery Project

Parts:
C53, C54, C55, C59: 4n7; C_0603_1608Metric; Voltage Rating 50V; Tolerance 10%
C56, C57, C58, C60: 100n; C_0603_1608Metric; Voltage Rating 10V; Tolerance 10%
J11: 874380643; MOLEX_874380643; MPN 874380843
R53, R54, R55: 2k2; R_0603_1608Metric; Tolerance 1%; Power Rating 1/10W
R56, R57, R58, R59: 10k; R_0603_1608Metric; Tolerance 1%; Power Rating 1/10W
R60: 0R; R_0603_1608Metric; Tolerance 1%; Power Rating 1/10W

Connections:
/FILTERS/HALL1_IN: C53.1, J11.3_1 (3), J11.3_2 (3), R53.2, R56.1
/FILTERS/HALL2_IN: C54.1, J11.4_1 (4), J11.4_2 (4), R54.2, R57.1
/FILTERS/HALL3_IN: C55.1, J11.5_1 (5), J11.5_2 (5), R55.2, R58.1
/FILTERS/TEMP_IN: C59.1, J11.2_1 (2), J11.2_2 (2), R59.1, R60.1
GND: C53.2, C54.2, C55.2, C56.2, C57.2, C58.2, C59.2, C60.2, J11.6_1 (6), J11.6_2 (6); also elsewhere on the board
HALL_1_OUT: R56.2; also elsewhere on the board
HALL_2_OUT: R57.2; also elsewhere on the board
HALL_3_OUT: R58.2; also elsewhere on the board
P3V3: C56.1, C57.1, C58.1, C60.1, R53.1, R54.1, R55.1, R59.2; also elsewhere on the board
P5V: J11.1_1 (1), J11.1_2 (1); also elsewhere on the board
TEMP_MOTOR: R60.2; also elsewhere on the board

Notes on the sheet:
HALL_2 FILTER
TEMP_MOTOR FILTER
HALL_1 FILTER
INPUT HALL ENCODER (TO MCU ==>)
HALL_3 FILTER
FILTERS
INPUT

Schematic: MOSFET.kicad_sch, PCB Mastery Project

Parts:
C48, C49: 2n2; C_0603_1608Metric; Voltage Rating 100V; Tolerance 10%
J7, J8, J9: 7461084; WP-BUTR_7461084; MPN 7461084
NT2, NT3, NT4, NT5: NetTie_2; NetTie-2_SMD_Pad0.5mm
Q1, Q2, Q3, Q4, Q5, Q6: HSBA15810C; MPN HSBA15810C
R34, R35, R40, R41, R46, R47: 4R7; R_0603_1608Metric; Tolerance 1%; Power Rating 1/10W
R36, R42, R48: 39k; R_0603_1608Metric; Tolerance 1%; Power Rating 1/10W
R37, R38, R43, R44: 100R; R_0603_1608Metric; Tolerance 1%; Power Rating 1/10W
R39, R45: 1m; WSLP2726_1mOHM_VIS; MPN WSLP27261L000FEA

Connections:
+VDC: Q1.5 (D), Q3.5 (D), Q5.5 (D); also elsewhere on the board
/MOSFET/M_H1_RG: Q1.4 (G), R34.2
/MOSFET/M_H2_RG: Q3.4 (G), R40.2
/MOSFET/M_H3_RG: Q5.4 (G), R46.2
/MOSFET/M_L1_RG: Q2.4 (G), R35.2, R36.1
/MOSFET/M_L2_RG: Q4.4 (G), R41.2, R42.1
/MOSFET/M_L3_RG: Q6.4 (G), R47.2, R48.1
/MOSFET/PHASE_1: J7.1, J7.2, J7.3, J7.4, J7.5, J7.6, J7.7, J7.8, NT2.2, Q1.1 (S), Q1.2 (S), Q1.3 (S), Q2.5 (D)
/MOSFET/PHASE_2: J8.1, J8.2, J8.3, J8.4, J8.5, J8.6, J8.7, J8.8, NT3.2, Q3.1 (S), Q3.2 (S), Q3.3 (S), Q4.5 (D)
/MOSFET/PHASE_3: J9.1, J9.2, J9.3, J9.4, J9.5, J9.6, J9.7, J9.8, NT4.2, Q5.1 (S), Q5.2 (S), Q5.3 (S), Q6.5 (D)
/MOSFET/SH1_N: R37.2, R39.3
/MOSFET/SH1_P: R38.2, R39.4
/MOSFET/SH2_N: R43.2, R45.3
/MOSFET/SH2_P: R44.2, R45.4
GND: NT5.1, R36.2, R39.2, R42.2, R45.2, R48.2; also elsewhere on the board
H1_LOW: Q2.1 (S), Q2.2 (S), Q2.3 (S), R39.1; also elsewhere on the board
H1_VS: NT2.1; also elsewhere on the board
H2_LOW: Q4.1 (S), Q4.2 (S), Q4.3 (S), R45.1; also elsewhere on the board
H2_VS: NT3.1; also elsewhere on the board
H3_LOW: NT5.2, Q6.1 (S), Q6.2 (S), Q6.3 (S); also elsewhere on the board
H3_VS: NT4.1; also elsewhere on the board
M_H1: R34.1; also elsewhere on the board
M_H2: R40.1; also elsewhere on the board
M_H3: R46.1; also elsewhere on the board
M_L1: R35.1; also elsewhere on the board
M_L2: R41.1; also elsewhere on the board
M_L3: R47.1; also elsewhere on the board
S1_N: C48.1, R37.1; also elsewhere on the board
S1_P: C48.2, R38.1; also elsewhere on the board
S2_N: C49.1, R43.1; also elsewhere on the board
S2_P: C49.2, R44.1; also elsewhere on the board

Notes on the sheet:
Q_CONTROL
Q_SOURCES
Kelving connection for sensing
SENSE L1
H#_VS
Place as close as possible to the bulk capacitanace
SENSE L2
M6 screw terminal
MCU SENSING FEEDBACK FOR EACH PHASE
OUTPUT PHASE 1
OUTPUT PHASE 2
Phase 1
Phase 3
OUTPUT PHASE 3
Phase 2
MOSFETs
